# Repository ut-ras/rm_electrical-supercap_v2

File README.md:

# rm_electrical-supercap_v2

So i heard that having a readme is good and professional, so if anyone bothers to read this and is curious:
    The objective of the project is to use the excess allowed power draw. We chose the 90W at the time of writing I believe.
    Started out with a half bridge topology for the buck boose to/from 24V:3V supercaps.
    Apparently many compromises were made because Jed (Ged?) didn't want to use a microcontroller.
    So now we're at full bridge, using mspm0, with a lot of sensors and stuff so that zero voltage switching can be implemented to avoid power loss spike
    This specific branch, is a redesign to minimize powerpath (mainly), since we have more depth looking into the robot in our little compartment of space.

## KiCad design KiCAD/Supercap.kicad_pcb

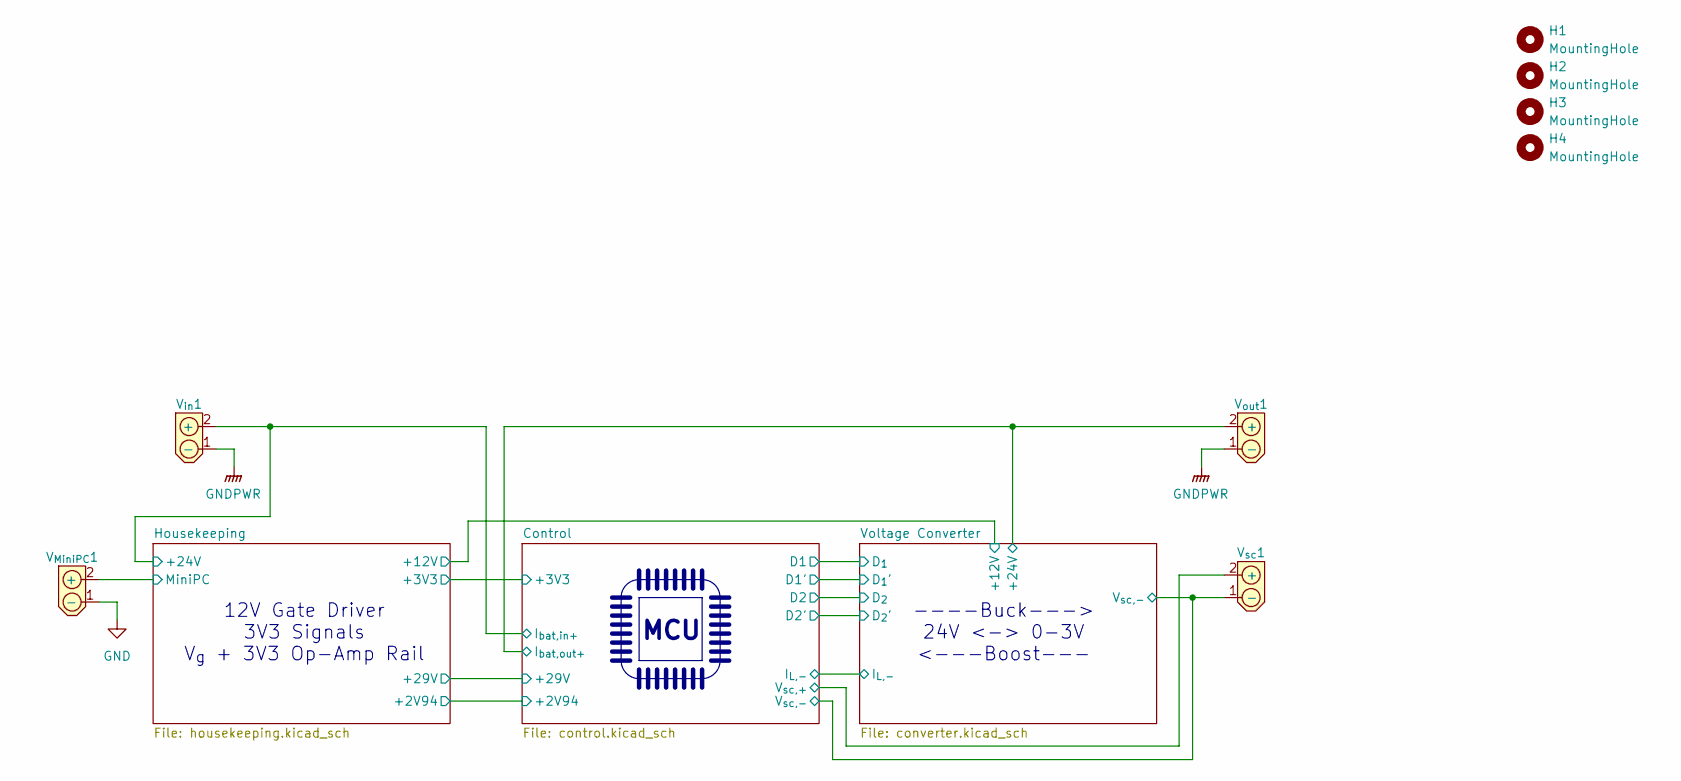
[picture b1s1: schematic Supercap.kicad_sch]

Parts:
H1, H2, H3, H4: MountingHole; MountingHole_2.2mm_M2_DIN965_Pad
V_{MiniPC}1: AMASS_XT30PW-M_1x02_P2.50mm_Horizontal
V_{in}1: AMASS_XT30PW-M_1x02_P2.50mm_Horizontal
V_{out}1: AMASS_XT30PW-F_1x02_P2.50mm_Horizontal
V_{sc}1: AMASS_XT30PW-F_1x02_P2.50mm_Horizontal

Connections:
/Control/I_{bat,out+}: V_{out}1.2 (+); also elsewhere on the board
/Control/V_{sc,+}: V_{sc}1.2 (+); also elsewhere on the board
/Housekeeping/+24V: V_{in}1.2 (+); also elsewhere on the board
/Housekeeping/MiniPC: V_{MiniPC}1.2 (+); also elsewhere on the board
/Voltage Converter/V_{sw,2}: V_{sc}1.1 (-); also elsewhere on the board
GND: V_{MiniPC}1.1 (-); also elsewhere on the board
GNDPWR: V_{in}1.1 (-), V_{out}1.1 (-); also elsewhere on the board

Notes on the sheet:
----Buck---> 24V <-> 0-3V <---Boost---
MCU
12V Gate Driver 3V3 Signals V_{g} + 3V3 Op-Amp Rail

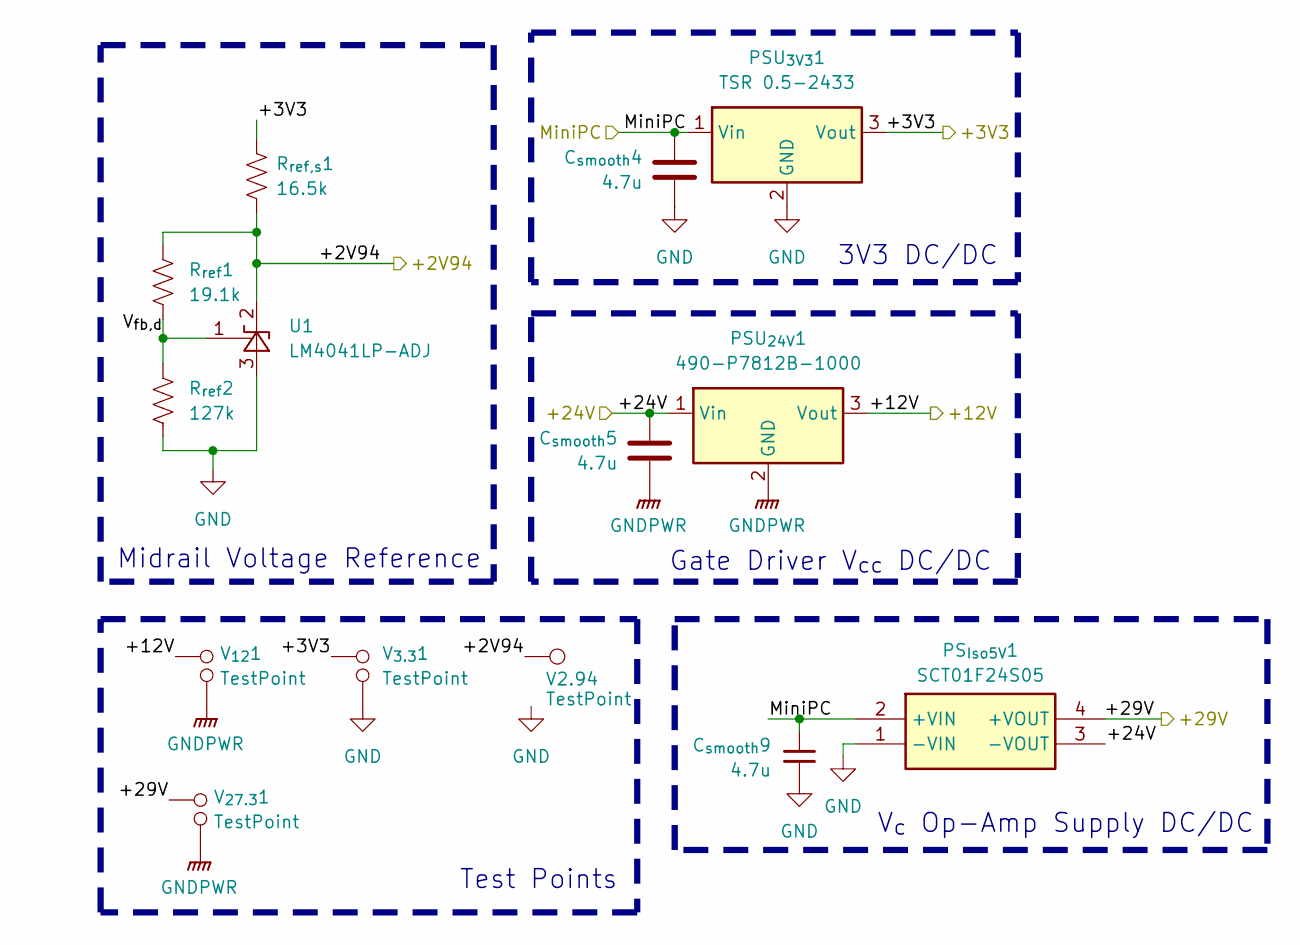
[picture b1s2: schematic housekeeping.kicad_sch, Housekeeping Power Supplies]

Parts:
C_{smooth}4, C_{smooth}5, C_{smooth}9: 4.7u; C_0603_1608Metric_Pad1.08x0.95mm_HandSolder; Manufacturer_Part_Number CL10A475KO8NNNC; Mouser Part Number 187-CL10A475KO8NNNC
PSU_{3V3}1: TSR 0.5-2433; Converter_DCDC_TRACO_TSR0.5-24xx_TSR0.5-24xxx_THT; Manufacturer_Part_Number 495-TSR0.5-2433; Mouser Part Number TSR 0.5-2433
PSU_{24V}1: 490-P7812B-1000; Converter_DCDC_TRACO_TSR0.5-24xx_TSR0.5-24xxx_THT; Manufacturer_Part_Number P7812B-1000; Mouser Part Number 490-P7812B-1000
PS_{Iso5V}1: SCT01F24S05; Converter_DCDC_TRACO_TEA1-xxxx_THT; Mouser Part Number 209-SCT01F24S05
R_{ref,s}1: 16.5k; R_0603_1608Metric_Pad0.98x0.95mm_HandSolder
R_{ref}1: 19.1k; R_0603_1608Metric_Pad0.98x0.95mm_HandSolder
R_{ref}2: 127k; R_0603_1608Metric_Pad0.98x0.95mm_HandSolder
U1: LM4041LP-ADJ; SOT-23
V2.94: TestPoint; TestPoint_Pad_1.5x1.5mm
V_{3.3}1, V_{12}1, V_{27.3}1: TestPoint; TP_Passive

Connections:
+3V3: PSU_{3V3}1.3 (Vout), R_{ref,s}1.1, V_{3.3}1.1; also elsewhere on the board
/Housekeeping/+2V94: R_{ref,s}1.2, R_{ref}1.1, U1.2 (K), V2.94.1 (1_1); also elsewhere on the board
/Housekeeping/+12V: PSU_{24V}1.3 (Vout), V_{12}1.1; also elsewhere on the board
/Housekeeping/+24V: C_{smooth}5.1, PSU_{24V}1.1 (Vin), PS_{Iso5V}1.3 (-VOUT); also elsewhere on the board
/Housekeeping/+29V: PS_{Iso5V}1.4 (+VOUT), V_{27.3}1.1; also elsewhere on the board
/Housekeeping/MiniPC: C_{smooth}4.1, C_{smooth}9.1, PSU_{3V3}1.1 (Vin), PS_{Iso5V}1.2 (+VIN); also elsewhere on the board
/Housekeeping/V_{fb,d}: R_{ref}1.2, R_{ref}2.1, U1.1 (FB)
GND: C_{smooth}4.2, C_{smooth}9.2, PSU_{3V3}1.2 (GND), PS_{Iso5V}1.1 (-VIN), R_{ref}2.2, U1.3 (A), V_{3.3}1.2; also elsewhere on the board
GNDPWR: C_{smooth}5.2, PSU_{24V}1.2 (GND), V_{12}1.2, V_{27.3}1.2; also elsewhere on the board

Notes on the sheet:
V_{c} Op-Amp Supply DC/DC
Gate Driver V_{cc} DC/DC
Midrail Voltage Reference
Test Points
3V3 DC/DC

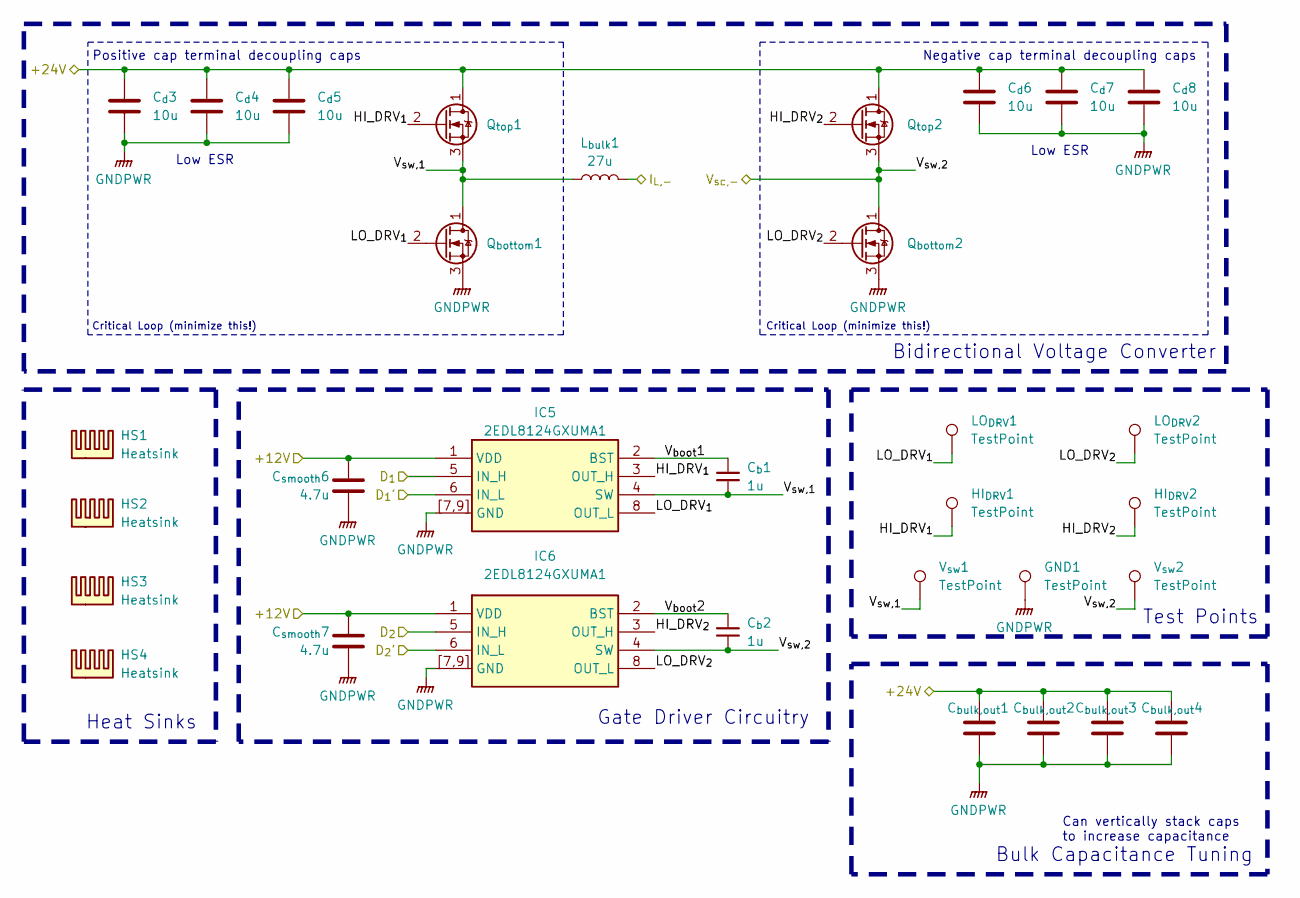
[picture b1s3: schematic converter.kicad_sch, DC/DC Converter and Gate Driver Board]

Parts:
C_{bulk,out}1, C_{bulk,out}2, C_{bulk,out}3, C_{bulk,out}4: C_1210_3225Metric_Pad1.33x2.70mm_HandSolder; Voltage Rating 50V
C_{b}1, C_{b}2: 1u; C_0603_1608Metric_Pad1.08x0.95mm_HandSolder; Manufacturer_Part_Number 963-MAJCT168BB7105KT; Mouser Part Number 963-MAJCT168BB7105KT
C_{d}3, C_{d}4, C_{d}5, C_{d}6, C_{d}7, C_{d}8: 10u; C_1210_3225Metric_Pad1.33x2.70mm_HandSolder; Voltage Rating 50V; Mouser Part Number 187-CL32B106KMVNNWE
C_{smooth}6, C_{smooth}7: 4.7u; C_0603_1608Metric_Pad1.08x0.95mm_HandSolder; Manufacturer_Part_Number CL10A475KO8NNNC; Mouser Part Number 187-CL10A475KO8NNNC
GND1: TestPoint; TestPoint_Keystone_5010-5014_Multipurpose
HI_{DRV}1, HI_{DRV}2: TestPoint; TestPoint_Keystone_5010-5014_Multipurpose
HS1, HS2, HS3, HS4: Heatsink; Manufacturer_Part_Number HSB01-080808; Mouser Part Number 490-HSB01-080808
IC5, IC6: 2EDL8124GXUMA1; SON80P400X400X100-9N-D; Mouser Part Number 726-2EDL8124GXUMA1
LO_{DRV}1, LO_{DRV}2: TestPoint; TestPoint_Keystone_5010-5014_Multipurpose
L_{bulk}1: 27u; L_Wurth_WE-HCFT-3635_74437636352702; Manufacturer_Part_Number 74437636352702; Mouser Part Number 710-74437636352702
Q_{bottom}1, Q_{bottom}2: IQDH45N04LM6CGSCATMA1; Manufacturer_Part_Number IQE020N04LM6CGSCATMA1; Mouser Part Number 726-IQE020N04LM6CGSC
Q_{top}1, Q_{top}2: IQDH45N04LM6CGSCATMA1; Manufacturer_Part_Number IQE020N04LM6CGSCATMA1; Mouser Part Number 726-IQE020N04LM6CGSC
V_{sw}1, V_{sw}2: TestPoint; TestPoint_Keystone_5010-5014_Multipurpose

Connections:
/Control/I_{L,-}: L_{bulk}1.2; also elsewhere on the board
/Control/I_{bat,out+}: C_{bulk,out}1.1, C_{bulk,out}2.1, C_{bulk,out}3.1, C_{bulk,out}4.1, C_{d}3.1, C_{d}4.1, C_{d}5.1, C_{d}6.1, C_{d}7.1, C_{d}8.1, Q_{top}1.1 (D), Q_{top}2.1 (D); also elsewhere on the board
/Control/TIMA0_C1: IC6.5 (IN_H); also elsewhere on the board
/Control/TIMA0_C1N: IC6.6 (IN_L); also elsewhere on the board
/Control/TIMA0_C3: IC5.5 (IN_H); also elsewhere on the board
/Control/TIMA0_C3N: IC5.6 (IN_L); also elsewhere on the board
/Housekeeping/+12V: C_{smooth}6.1, C_{smooth}7.1, IC5.1 (VDD), IC6.1 (VDD); also elsewhere on the board
/Voltage Converter/HI_DRV_{1}: HI_{DRV}1.1 (1_1), IC5.3 (OUT_H), Q_{top}1.2 (G)
/Voltage Converter/HI_DRV_{2}: HI_{DRV}2.1 (1_1), IC6.3 (OUT_H), Q_{top}2.2 (G)
/Voltage Converter/LO_DRV_{1}: IC5.8 (OUT_L), LO_{DRV}1.1 (1_1), Q_{bottom}1.2 (G)
/Voltage Converter/LO_DRV_{2}: IC6.8 (OUT_L), LO_{DRV}2.1 (1_1), Q_{bottom}2.2 (G)
/Voltage Converter/V_{boot}1: C_{b}1.1, IC5.2 (BST)
/Voltage Converter/V_{boot}2: C_{b}2.1, IC6.2 (BST)
/Voltage Converter/V_{sw,1}: C_{b}1.2, IC5.4 (SW), L_{bulk}1.1, Q_{bottom}1.1 (D), Q_{top}1.3 (S), V_{sw}1.1 (1_1)
/Voltage Converter/V_{sw,2}: C_{b}2.2, IC6.4 (SW), Q_{bottom}2.1 (D), Q_{top}2.3 (S), V_{sw}2.1 (1_1); also elsewhere on the board
GNDPWR: C_{bulk,out}1.2, C_{bulk,out}2.2, C_{bulk,out}3.2, C_{bulk,out}4.2, C_{d}3.2, C_{d}4.2, C_{d}5.2, C_{d}6.2, C_{d}7.2, C_{d}8.2, C_{smooth}6.2, C_{smooth}7.2, GND1.1 (1_1), IC5.7 (GND), IC5.9 (GND), IC5.[7,9] (GND), IC6.7 (GND), IC6.9 (GND), IC6.[7,9] (GND), Q_{bottom}1.3 (S), Q_{bottom}2.3 (S); also elsewhere on the board

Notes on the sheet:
Heat Sinks
Critical Loop (minimize this!)
Negative cap terminal decoupling caps
Test Points
Bidirectional Voltage Converter
Bulk Capacitance Tuning
Gate Driver Circuitry
Low ESR
Can vertically stack caps to increase capacitance
Positive cap terminal decoupling caps

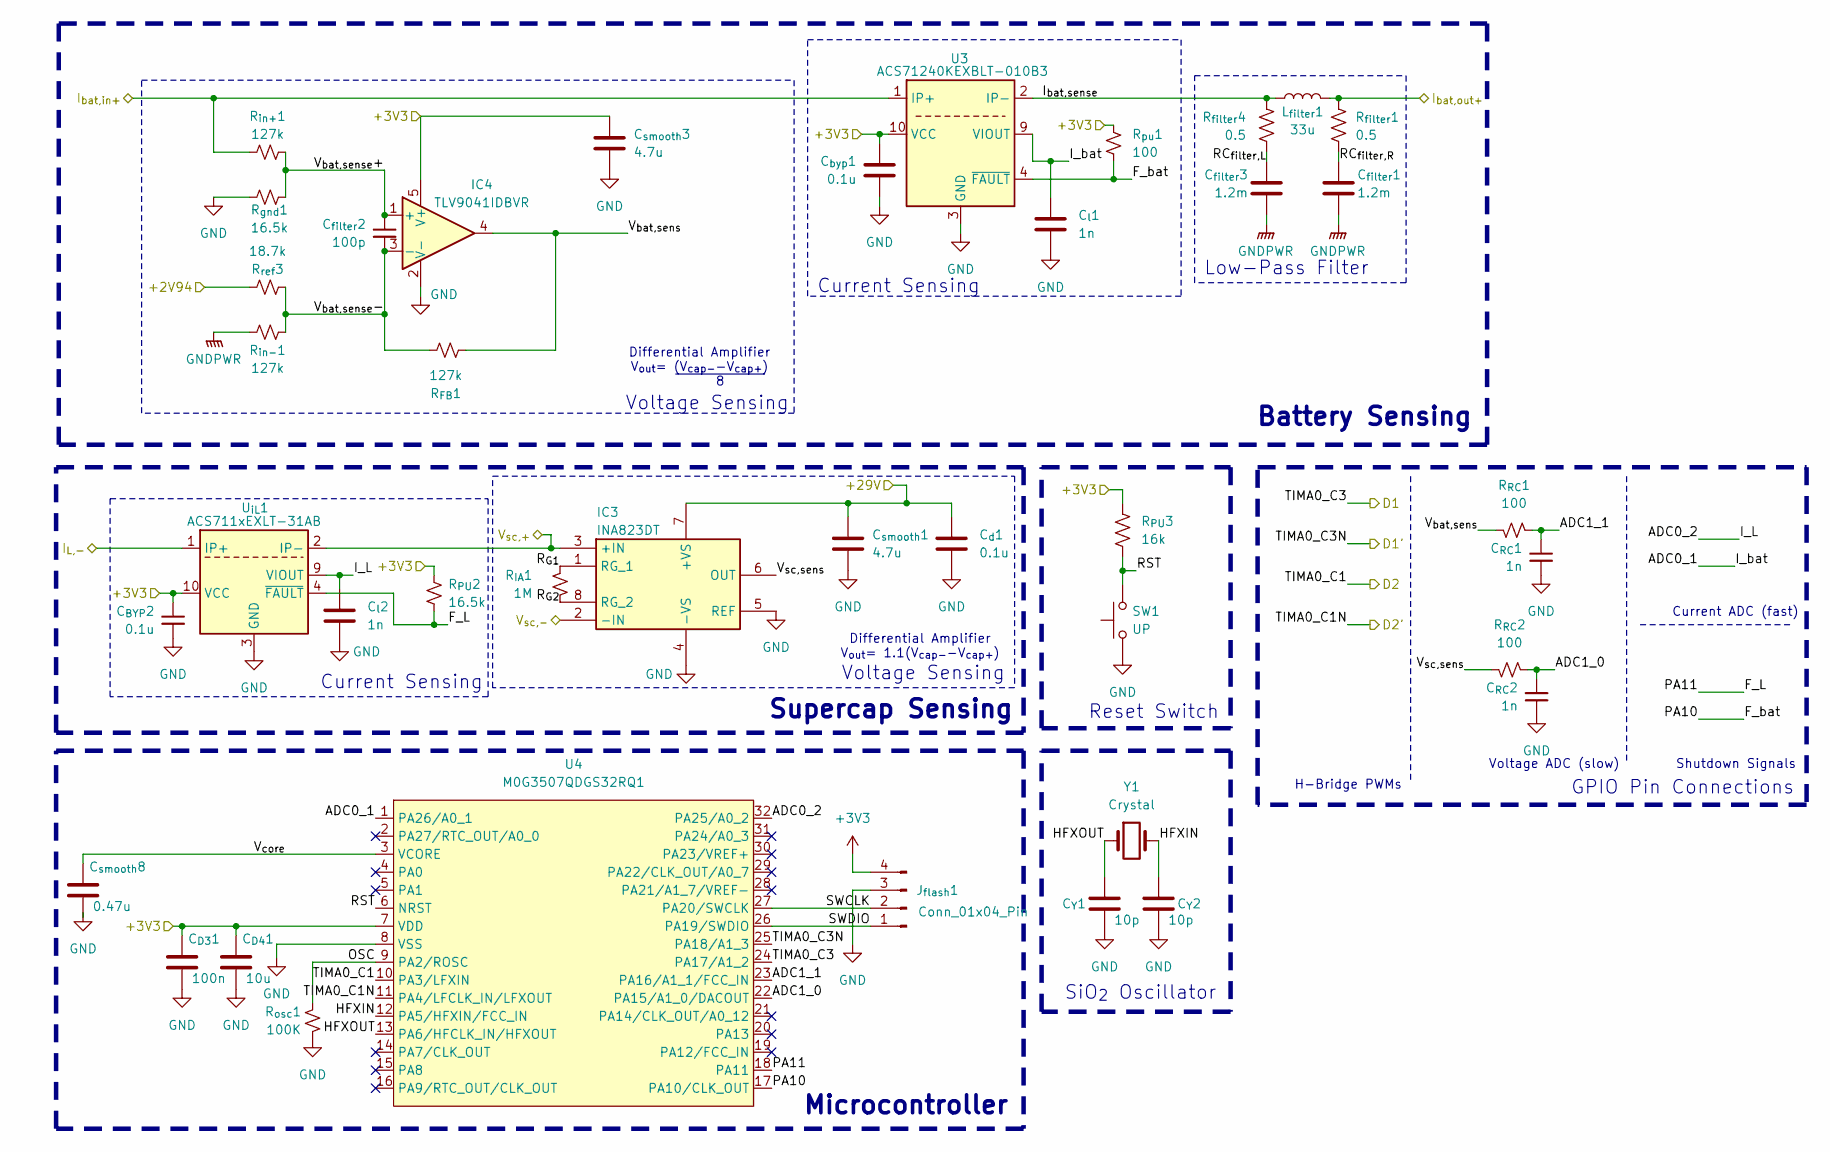
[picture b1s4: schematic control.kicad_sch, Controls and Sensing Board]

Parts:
C_{BYP}2: 0.1u; C_0603_1608Metric_Pad1.08x0.95mm_HandSolder; Mouser# 581-0603YC104M
C_{D3}1: 100n; C_0402_1005Metric_Pad0.74x0.62mm_HandSolder; Mouser# 581-KGM05AR71C104JH
C_{D4}1: 10u; C_0402_1005Metric_Pad0.74x0.62mm_HandSolder; Mouser# 81-GRM155R60G106ME1D
C_{RC}1, C_{RC}2: 1n; C_0603_1608Metric_Pad1.08x0.95mm_HandSolder; Manufacturer_Part_Number CC0603JRX7R7BB102; Mouser Part Number 603-CC0603JR7R7BB102
C_{Y}1, C_{Y}2: 10p; C_0603_1608Metric_Pad1.08x0.95mm_HandSolder; Mouser# 660-NPO0603HTTD100J
C_{byp}1: 0.1u; C_0603_1608Metric_Pad1.08x0.95mm_HandSolder; Manufacturer_Part_Number MCAST168SB5104KTNA01; Mouser Part Number 963-MCAST168SB5104KT
C_{d}1: 0.1u; C_0603_1608Metric_Pad1.08x0.95mm_HandSolder; Manufacturer_Part_Number MCAST168SB5104KTNA01; Mouser Part Number 963-MCAST168SB5104KT
C_{filter}1, C_{filter}3: 1.2m; C_Radial_D10.0mm_H20.0mm_P5.00mm; Mouser# 80-A7D0MW128M1EAAS11
C_{filter}2: 100p; C_0603_1608Metric_Pad1.08x0.95mm_HandSolder; Manufacturer_Part_Number CC0603JPNPO9BN101; Mouser Part Number 603-CC603JPNPO9BN101
C_{l}1, C_{l}2: 1n; C_0603_1608Metric_Pad1.08x0.95mm_HandSolder; Manufacturer_Part_Number CC0603JRX7R7BB102; Mouser Part Number 603-CC0603JR7R7BB102
C_{smooth}1, C_{smooth}3: 4.7u; C_0603_1608Metric_Pad1.08x0.95mm_HandSolder; Manufacturer_Part_Number MCAST168SB5104KTNA01; Mouser Part Number 963-MCAST168SB5104KT
C_{smooth}8: 0.47u; C_0603_1608Metric_Pad1.08x0.95mm_HandSolder; Manufacturer_Part_Number CL10B474KO8NNND; Mouser Part Number 187-CL10B474KO8NNND
IC3: INA823DT; SOIC127P600X175-8N; Mouser Part Number 595-INA823DT
IC4: TLV9041IDBVR; DBV0005A-IPC_A
J_{flash}1: Conn_01x04_Pin; PinSocket_2x02_P2.54mm_Vertical
L_{filter}1: 33u; 74436413300; Manufacturer_Part_Number 74436413300; Mouser Part Number 710-74436413300
R_{FB}1: 127k; R_0603_1608Metric_Pad0.98x0.95mm_HandSolder; Manufacturer_Part_Number CRGCQ0603F100R; Mouser Part Number 279-CRGCQ0603F100R
R_{IA}1: 1M; R_0603_1608Metric_Pad0.98x0.95mm_HandSolder; Manufacturer_Part_Number CRGCQ0603F100R; Mouser Part Number 279-CRGCQ0603F100R
R_{PU}2: 16.5k; R_0603_1608Metric_Pad0.98x0.95mm_HandSolder; Manufacturer_Part_Number CRGCQ0603J1K0; Mouser Part Number 279-CRGCQ0603J1K0
R_{PU}3: 16k; R_0603_1608Metric_Pad0.98x0.95mm_HandSolder
R_{RC}1, R_{RC}2: 100; R_0603_1608Metric_Pad0.98x0.95mm_HandSolder; Manufacturer_Part_Number CRGCQ0603F100R; Mouser Part Number 279-CRGCQ0603F100R
R_{filter}1, R_{filter}4: 0.5; R_0805_2012Metric_Pad1.20x1.40mm_HandSolder; Manufacturer_Part_Number RL1220S-R50-F; Mouser Part Number 754-RL1220S-R50-F
R_{gnd}1: 16.5k; R_0603_1608Metric_Pad0.98x0.95mm_HandSolder; Manufacturer_Part_Number CRGCQ0603F100R; Mouser Part Number 279-CRGCQ0603F100R
R_{in+}1: 127k; R_0603_1608Metric_Pad0.98x0.95mm_HandSolder; Manufacturer_Part_Number CRGCQ0603F100R; Mouser Part Number 279-CRGCQ0603F100R
R_{in-}1: 127k; R_0603_1608Metric_Pad0.98x0.95mm_HandSolder; Manufacturer_Part_Number CRGCQ0603F100R; Mouser Part Number 279-CRGCQ0603F100R
R_{osc}1: 100K; R_0603_1608Metric_Pad0.98x0.95mm_HandSolder; Manufacturer_Part_Number RN73R1JTTD1003B25; Mouser Part Number 660-RN73R1JTD1003B25
R_{pu}1: 100; R_0603_1608Metric_Pad0.98x0.95mm_HandSolder; Manufacturer_Part_Number CRGCQ0603F100R; Mouser Part Number 279-CRGCQ0603F100R
R_{ref}3: 18.7k; R_0603_1608Metric_Pad0.98x0.95mm_HandSolder; Manufacturer_Part_Number CRGCQ0603F100R; Mouser Part Number 279-CRGCQ0603F100R
SW1: UP; SW_PUSH_6mm
U3: ACS71240KEXBLT-010B3; Allegro_QFN-12-10-1EP_3x3mm_P0.5mm; Manufacturer_Part_Number ACS71240KEXBLT-010B3; Mouser Part Number 250-71240KEXBLT010B3
U4: M0G3507QDGS32RQ1; VSSOP_0.5mm_32pin_handsolder
U_{iL}1: ACS711xEXLT-31AB; Allegro_QFN-12-10-1EP_3x3mm_P0.5mm
Y1: Crystal; Crystal_SMD_Abracon_ABM3-2Pin_5.0x3.2mm

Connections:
+3V3: C_{BYP}2.1, C_{D3}1.1, C_{D4}1.1, C_{byp}1.1, C_{smooth}3.1, IC4.5 (V+), J_{flash}1.4, R_{PU}2.2, R_{PU}3.1, R_{pu}1.2, U3.10 (VCC), U4.7 (VDD), U_{iL}1.10 (VCC); also elsewhere on the board
/Control/ADC0_1: C_{l}1.1, U3.9 (VIOUT), U4.1 (PA26/A0_1)
/Control/ADC0_2: C_{l}2.1, U4.32 (PA25/A0_2), U_{iL}1.9 (VIOUT)
/Control/ADC1_0: C_{RC}2.1, R_{RC}2.2, U4.22 (PA15/A1_0/DACOUT)
/Control/ADC1_1: C_{RC}1.1, R_{RC}1.2, U4.23 (PA16/A1_1/FCC_IN)
/Control/F_L: R_{PU}2.1, U4.18 (PA11), U_{iL}1.4 (~FAULT)
/Control/F_bat: R_{pu}1.1, U3.4 (~FAULT), U4.17 (PA10/CLK_OUT)
/Control/HFXIN: C_{Y}2.1, U4.12 (PA5/HFXIN/FCC_IN), Y1.2
/Control/HFXOUT: C_{Y}1.1, U4.13 (PA6/HFCLK_IN/HFXOUT), Y1.1
/Control/I_{L,-}: U_{iL}1.1 (IP+); also elsewhere on the board
/Control/I_{bat,out+}: L_{filter}1.2, R_{filter}1.1; also elsewhere on the board
/Control/I_{bat,sense}: L_{filter}1.1, R_{filter}4.1, U3.2 (IP-)
/Control/OSC: R_{osc}1.1, U4.9 (PA2/ROSC)
/Control/RC_{filter,L}: C_{filter}3.1, R_{filter}4.2
/Control/RC_{filter,R}: C_{filter}1.1, R_{filter}1.2
/Control/RST: R_{PU}3.2, SW1.2, U4.6 (NRST)
/Control/R_{G1}: IC3.1 (RG_1), R_{IA}1.1
/Control/R_{G2}: IC3.8 (RG_2), R_{IA}1.2
/Control/SWCLK: J_{flash}1.2, U4.27 (PA20/SWCLK)
/Control/SWDIO: J_{flash}1.1, U4.26 (PA19/SWDIO)
/Control/TIMA0_C1: U4.10 (PA3/LFXIN); also elsewhere on the board
/Control/TIMA0_C1N: U4.11 (PA4/LFCLK_IN/LFXOUT); also elsewhere on the board
/Control/TIMA0_C3: U4.24 (PA17/A1_2); also elsewhere on the board
/Control/TIMA0_C3N: U4.25 (PA18/A1_3); also elsewhere on the board
/Control/V_{bat,sense}+: C_{filter}2.1, IC4.1 (+), R_{gnd}1.1, R_{in+}1.1
/Control/V_{bat,sense}-: C_{filter}2.2, IC4.3 (-), R_{FB}1.1, R_{in-}1.1, R_{ref}3.2
/Control/V_{bat,sens}: IC4.4, R_{FB}1.2, R_{RC}1.1
/Control/V_{core}: C_{smooth}8.1, U4.3 (VCORE)
/Control/V_{sc,+}: IC3.3 (+IN), U_{iL}1.2 (IP-); also elsewhere on the board
/Control/V_{sc,sens}: IC3.6 (OUT), R_{RC}2.1
/Housekeeping/+2V94: R_{ref}3.1; also elsewhere on the board
/Housekeeping/+24V: R_{in+}1.2, U3.1 (IP+); also elsewhere on the board
/Housekeeping/+29V: C_{d}1.1, C_{smooth}1.1, IC3.7 (+VS); also elsewhere on the board
/Voltage Converter/V_{sw,2}: IC3.2 (-IN); also elsewhere on the board
GND: C_{BYP}2.2, C_{D3}1.2, C_{D4}1.2, C_{RC}1.2, C_{RC}2.2, C_{Y}1.2, C_{Y}2.2, C_{byp}1.2, C_{d}1.2, C_{l}1.2, C_{l}2.2, C_{smooth}1.2, C_{smooth}3.2, C_{smooth}8.2, IC3.4 (-VS), IC3.5 (REF), IC4.2 (V-), J_{flash}1.3, R_{gnd}1.2, R_{osc}1.2, SW1.1, U3.3 (GND), U4.8 (VSS), U_{iL}1.3 (GND); also elsewhere on the board
GNDPWR: C_{filter}1.2, C_{filter}3.2, R_{in-}1.2; also elsewhere on the board

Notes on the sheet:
Shutdown Signals
Microcontroller
Voltage Sensing
Supercap Sensing
Current ADC (fast)
Current Sensing
Low-Pass Filter
Voltage ADC (slow)
SiO_{2} Oscillator
Differential Amplifier V_{out}= (V_{cap-}-V_{cap+}) ~{ 8 }
Reset Switch
GPIO Pin Connections
H-Bridge PWMs
Battery Sensing
Differential Amplifier V_{out}= 1.1(V_{cap-}-V_{cap+})

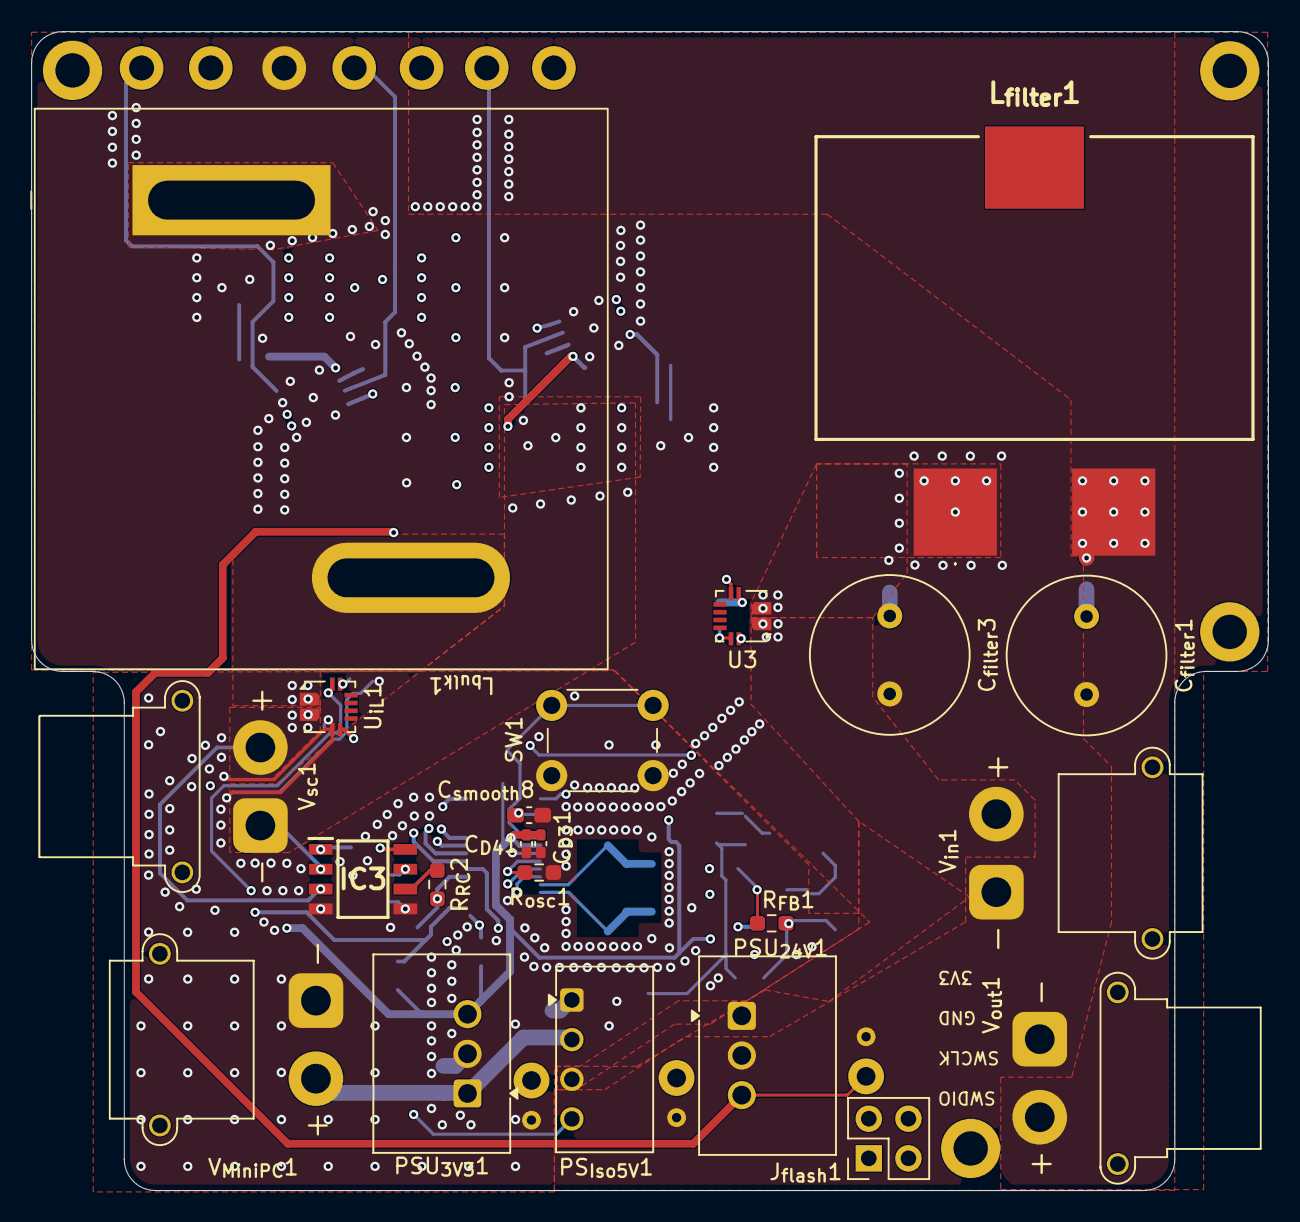
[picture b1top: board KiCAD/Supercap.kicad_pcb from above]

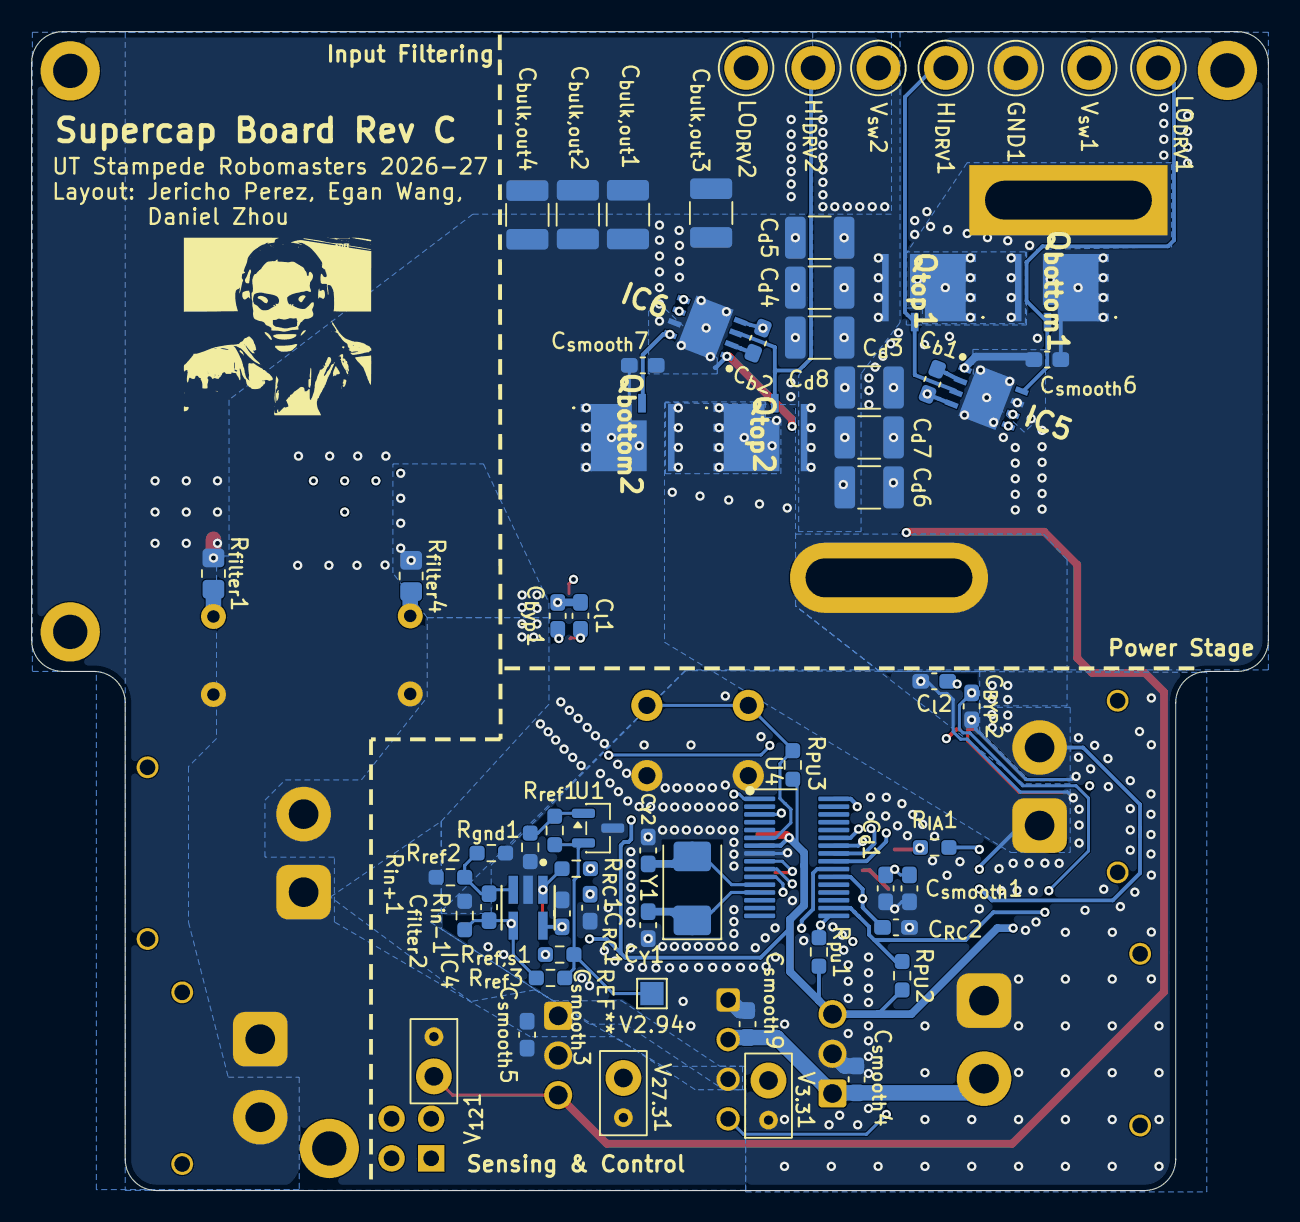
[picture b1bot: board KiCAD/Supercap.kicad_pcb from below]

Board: 4 copper layers, 79.2 x 74.3 mm, 90 parts (67 on the bottom side), 46 nets.

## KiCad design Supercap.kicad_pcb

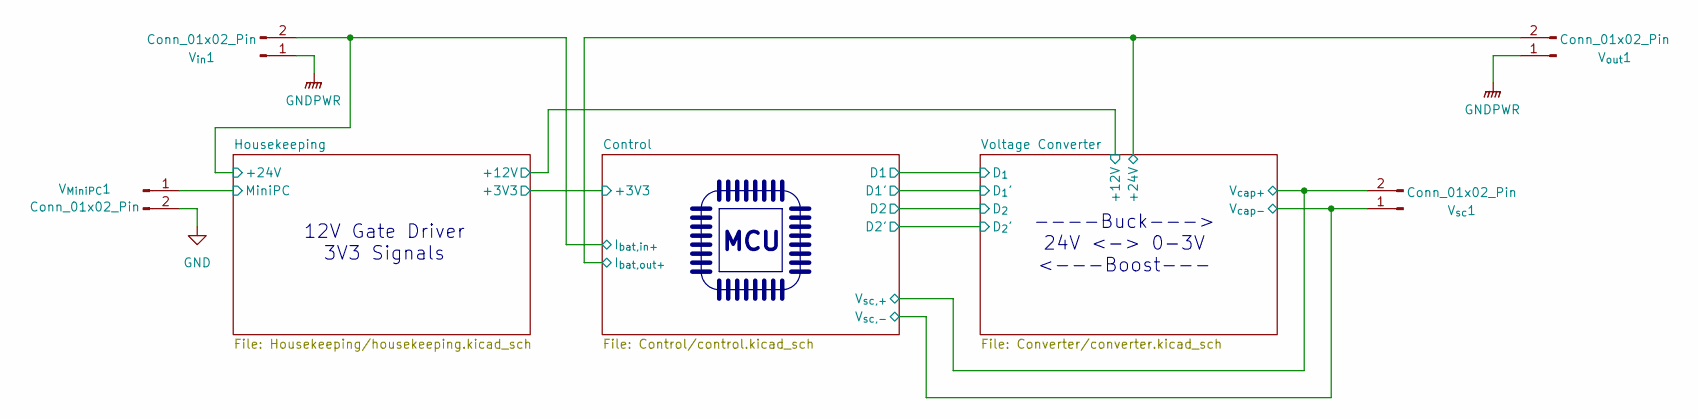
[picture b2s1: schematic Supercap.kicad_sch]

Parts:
V_{MiniPC}1: Conn_01x02_Pin; AMASS_XT30PW-F_1x02_P2.50mm_Horizontal
V_{in}1: Conn_01x02_Pin; AMASS_XT30PW-M_1x02_P2.50mm_Horizontal
V_{out}1: Conn_01x02_Pin; AMASS_XT30PW-F_1x02_P2.50mm_Horizontal
V_{sc}1: Conn_01x02_Pin; AMASS_XT30PW-M_1x02_P2.50mm_Horizontal

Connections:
/Control/I_{bat,in+}: V_{in}1.2; also elsewhere on the board
/Control/I_{bat,out+}: V_{out}1.2; also elsewhere on the board
/Control/V_{sc,+}: V_{sc}1.2; also elsewhere on the board
/Housekeeping/MiniPC: V_{MiniPC}1.1; also elsewhere on the board
/Voltage Converter/V_{sw,2}: V_{sc}1.1; also elsewhere on the board
GND: V_{MiniPC}1.2; also elsewhere on the board
GNDPWR: V_{in}1.1, V_{out}1.1; also elsewhere on the board

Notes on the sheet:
----Buck---> 24V <-> 0-3V <---Boost---
MCU
12V Gate Driver 3V3 Signals

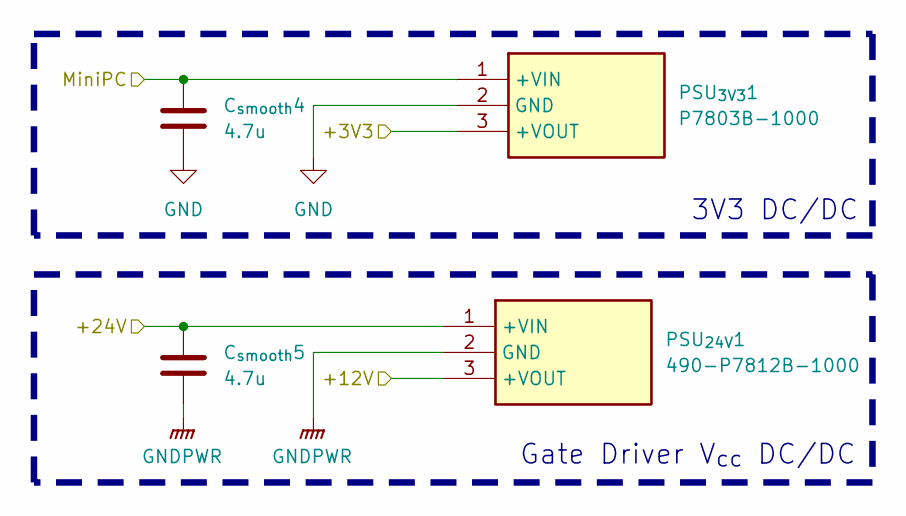
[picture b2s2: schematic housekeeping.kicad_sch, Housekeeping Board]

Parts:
C_{smooth}4, C_{smooth}5: 4.7u; C_0603_1608Metric_Pad1.08x0.95mm_HandSolder; Manufacturer_Part_Number CL10A475KO8NNNC; Mouser Part Number 187-CL10A475KO8NNNC
PSU_{3V3}1: P7803B-1000; P7812B1000; Manufacturer_Part_Number P7803B-1000; Mouser Part Number 490-P7803B-1000
PSU_{24V}1: 490-P7812B-1000; P7812B1000; Manufacturer_Part_Number P7812B-1000; Mouser Part Number 490-P7812B-1000

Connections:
/Control/+3V3: PSU_{3V3}1.3 (+VOUT); also elsewhere on the board
/Control/I_{bat,in+}: C_{smooth}5.1, PSU_{24V}1.1 (+VIN); also elsewhere on the board
/Housekeeping/+12V: PSU_{24V}1.3 (+VOUT); also elsewhere on the board
/Housekeeping/MiniPC: C_{smooth}4.1, PSU_{3V3}1.1 (+VIN); also elsewhere on the board
GND: C_{smooth}4.2, PSU_{3V3}1.2 (GND); also elsewhere on the board
GNDPWR: C_{smooth}5.2, PSU_{24V}1.2 (GND); also elsewhere on the board

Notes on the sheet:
Gate Driver V_{cc} DC/DC
3V3 DC/DC

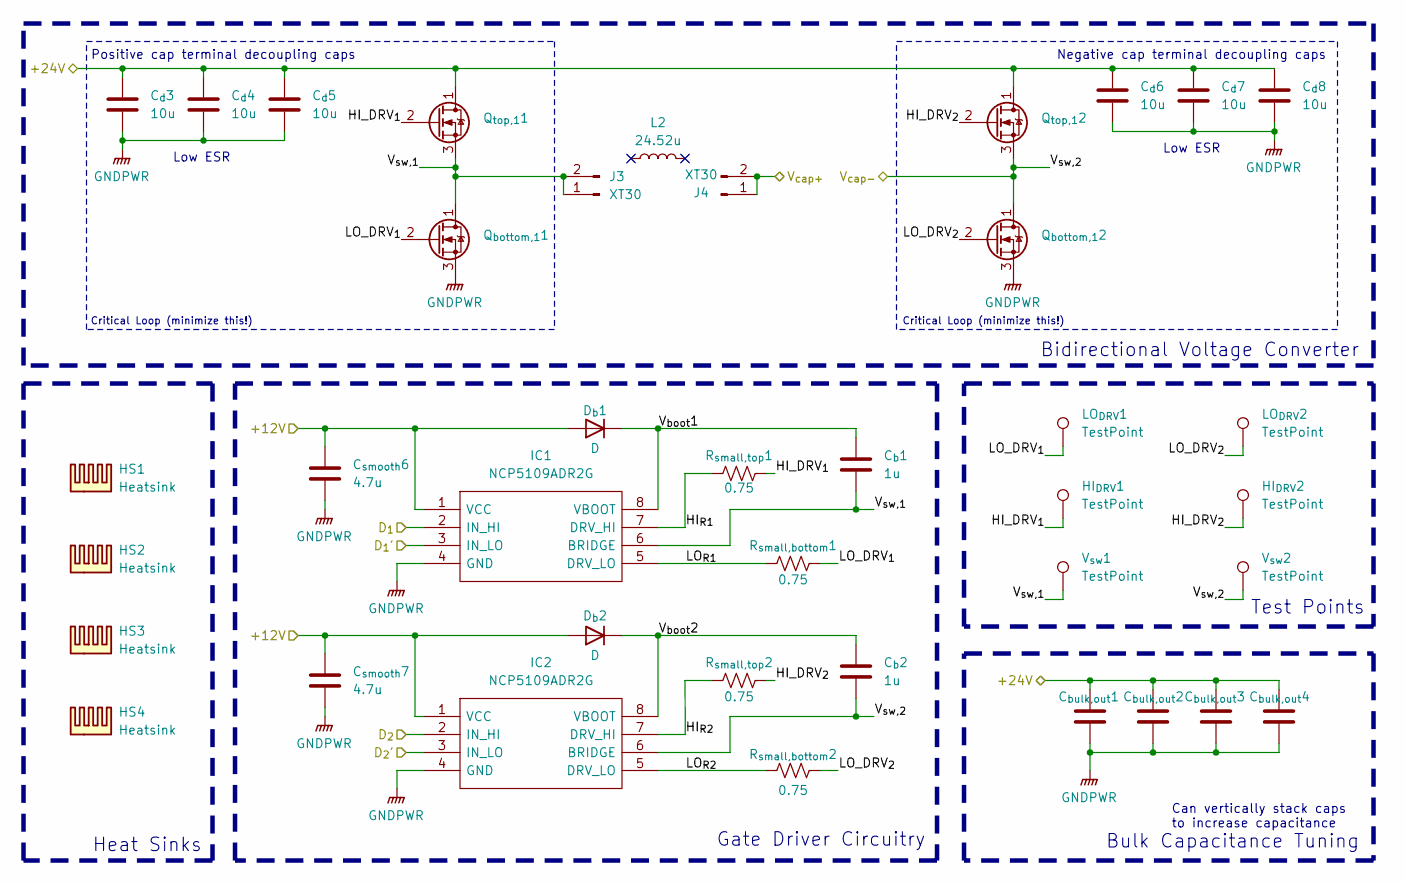
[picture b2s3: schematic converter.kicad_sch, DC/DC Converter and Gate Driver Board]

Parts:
C_{bulk,out}1, C_{bulk,out}2, C_{bulk,out}3, C_{bulk,out}4: C_0603_1608Metric_Pad1.08x0.95mm_HandSolder; Voltage Rating 50V
C_{b}1, C_{b}2: 1u; C_0603_1608Metric_Pad1.08x0.95mm_HandSolder; Manufacturer_Part_Number 963-MAJCT168BB7105KT; Mouser Part Number 963-MAJCT168BB7105KT
C_{d}3, C_{d}4, C_{d}5, C_{d}6, C_{d}7, C_{d}8: 10u; C_1210_3225Metric_Pad1.33x2.70mm_HandSolder; Voltage Rating 50V; Mouser Part Number 187-CL32B106KMVNNWE
C_{smooth}6, C_{smooth}7: 4.7u; C_0603_1608Metric_Pad1.08x0.95mm_HandSolder; Manufacturer_Part_Number CL10A475KO8NNNC; Mouser Part Number 187-CL10A475KO8NNNC
D_{b}1, D_{b}2: D; D_MicroSMP_AK; Manufacturer_Part_Number V1P22HM3_A/H; Mouser Part Number 78-V1P22HM3_A/H
HI_{DRV}1, HI_{DRV}2: TestPoint; TestPoint_Bridge_Pitch2.0mm_Drill0.7mm
HS1, HS2, HS3, HS4: Heatsink; Manufacturer_Part_Number HSB01-080808; Mouser Part Number 490-HSB01-080808
IC1, IC2: NCP5109ADR2G; SOIC127P600X175-8N; Mouser Part Number 863-NCP5109ADR2G
J3, J4: XT30; AMASS_XT30UPB-F_1x02_P5.0mm_Vertical
L2: 24.52u
LO_{DRV}1, LO_{DRV}2: TestPoint; TestPoint_Bridge_Pitch2.0mm_Drill0.7mm
Q_{bottom,1}1, Q_{bottom,1}2: IQDH45N04LM6CGSCATMA1; Manufacturer_Part_Number IQDH35N03LM5CGSCATMA1; Mouser Part Number 726-IQDH35N03LM5CGSC
Q_{top,1}1, Q_{top,1}2: IQDH45N04LM6CGSCATMA1; Manufacturer_Part_Number IQDH35N03LM5CGSCATMA1; Mouser Part Number 726-IQDH35N03LM5CGSC
R_{small,bottom}1, R_{small,bottom}2: 0.75; R_0603_1608Metric_Pad0.98x0.95mm_HandSolder; Manufacturer_Part_Number RL0603FR-070R75L; Mouser Part Number 603-RL0603FR-070R75L
R_{small,top}1, R_{small,top}2: 0.75; R_0603_1608Metric_Pad0.98x0.95mm_HandSolder; Manufacturer_Part_Number RL0603FR-070R75L; Mouser Part Number 603-RL0603FR-070R75L
V_{sw}1, V_{sw}2: TestPoint; TestPoint_Bridge_Pitch2.0mm_Drill0.7mm

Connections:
/Control/I_{bat,out+}: C_{bulk,out}1.1, C_{bulk,out}2.1, C_{bulk,out}3.1, C_{bulk,out}4.1, C_{d}3.1, C_{d}4.1, C_{d}5.1, C_{d}6.1, C_{d}7.1, C_{d}8.1, Q_{top,1}1.1 (D), Q_{top,1}2.1 (D); also elsewhere on the board
/Control/PA8: IC1.2 (IN_HI); also elsewhere on the board
/Control/PA22: IC1.3 (IN_LO); also elsewhere on the board
/Control/PA25: IC2.3 (IN_LO); also elsewhere on the board
/Control/PB9: IC2.2 (IN_HI); also elsewhere on the board
/Control/V_{sc,+}: J4.1, J4.2; also elsewhere on the board
/Housekeeping/+12V: C_{smooth}6.1, C_{smooth}7.1, D_{b}1.2 (A), D_{b}2.2 (A), IC1.1 (VCC), IC2.1 (VCC); also elsewhere on the board
/Voltage Converter/HI_DRV_{1}: HI_{DRV}1.1, Q_{top,1}1.2 (G), R_{small,top}1.2
/Voltage Converter/HI_DRV_{2}: HI_{DRV}2.1, Q_{top,1}2.2 (G), R_{small,top}2.2
/Voltage Converter/HI_{R1}: IC1.7 (DRV_HI), R_{small,top}1.1
/Voltage Converter/HI_{R2}: IC2.7 (DRV_HI), R_{small,top}2.1
/Voltage Converter/LO_DRV_{1}: LO_{DRV}1.1, Q_{bottom,1}1.2 (G), R_{small,bottom}1.2
/Voltage Converter/LO_DRV_{2}: LO_{DRV}2.1, Q_{bottom,1}2.2 (G), R_{small,bottom}2.2
/Voltage Converter/LO_{R1}: IC1.5 (DRV_LO), R_{small,bottom}1.1
/Voltage Converter/LO_{R2}: IC2.5 (DRV_LO), R_{small,bottom}2.1
/Voltage Converter/V_{boot}1: C_{b}1.1, D_{b}1.1 (K), IC1.8 (VBOOT)
/Voltage Converter/V_{boot}2: C_{b}2.1, D_{b}2.1 (K), IC2.8 (VBOOT)
/Voltage Converter/V_{sw,1}: C_{b}1.2, IC1.6 (BRIDGE), J3.1, J3.2, Q_{bottom,1}1.1 (D), Q_{top,1}1.3 (S), V_{sw}1.1
/Voltage Converter/V_{sw,2}: C_{b}2.2, IC2.6 (BRIDGE), Q_{bottom,1}2.1 (D), Q_{top,1}2.3 (S), V_{sw}2.1; also elsewhere on the board
GNDPWR: C_{bulk,out}1.2, C_{bulk,out}2.2, C_{bulk,out}3.2, C_{bulk,out}4.2, C_{d}3.2, C_{d}4.2, C_{d}5.2, C_{d}6.2, C_{d}7.2, C_{d}8.2, C_{smooth}6.2, C_{smooth}7.2, IC1.4 (GND), IC2.4 (GND), Q_{bottom,1}1.3 (S), Q_{bottom,1}2.3 (S); also elsewhere on the board

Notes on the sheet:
Heat Sinks
Critical Loop (minimize this!)
Negative cap terminal decoupling caps
Test Points
Bidirectional Voltage Converter
Bulk Capacitance Tuning
Gate Driver Circuitry
Low ESR
Can vertically stack caps to increase capacitance
Positive cap terminal decoupling caps
